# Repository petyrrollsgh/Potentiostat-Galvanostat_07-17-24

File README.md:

# Potentiostat-Galvanostat_07-17-24
KiCad files for the initial Potentiostat-Glavanostat build

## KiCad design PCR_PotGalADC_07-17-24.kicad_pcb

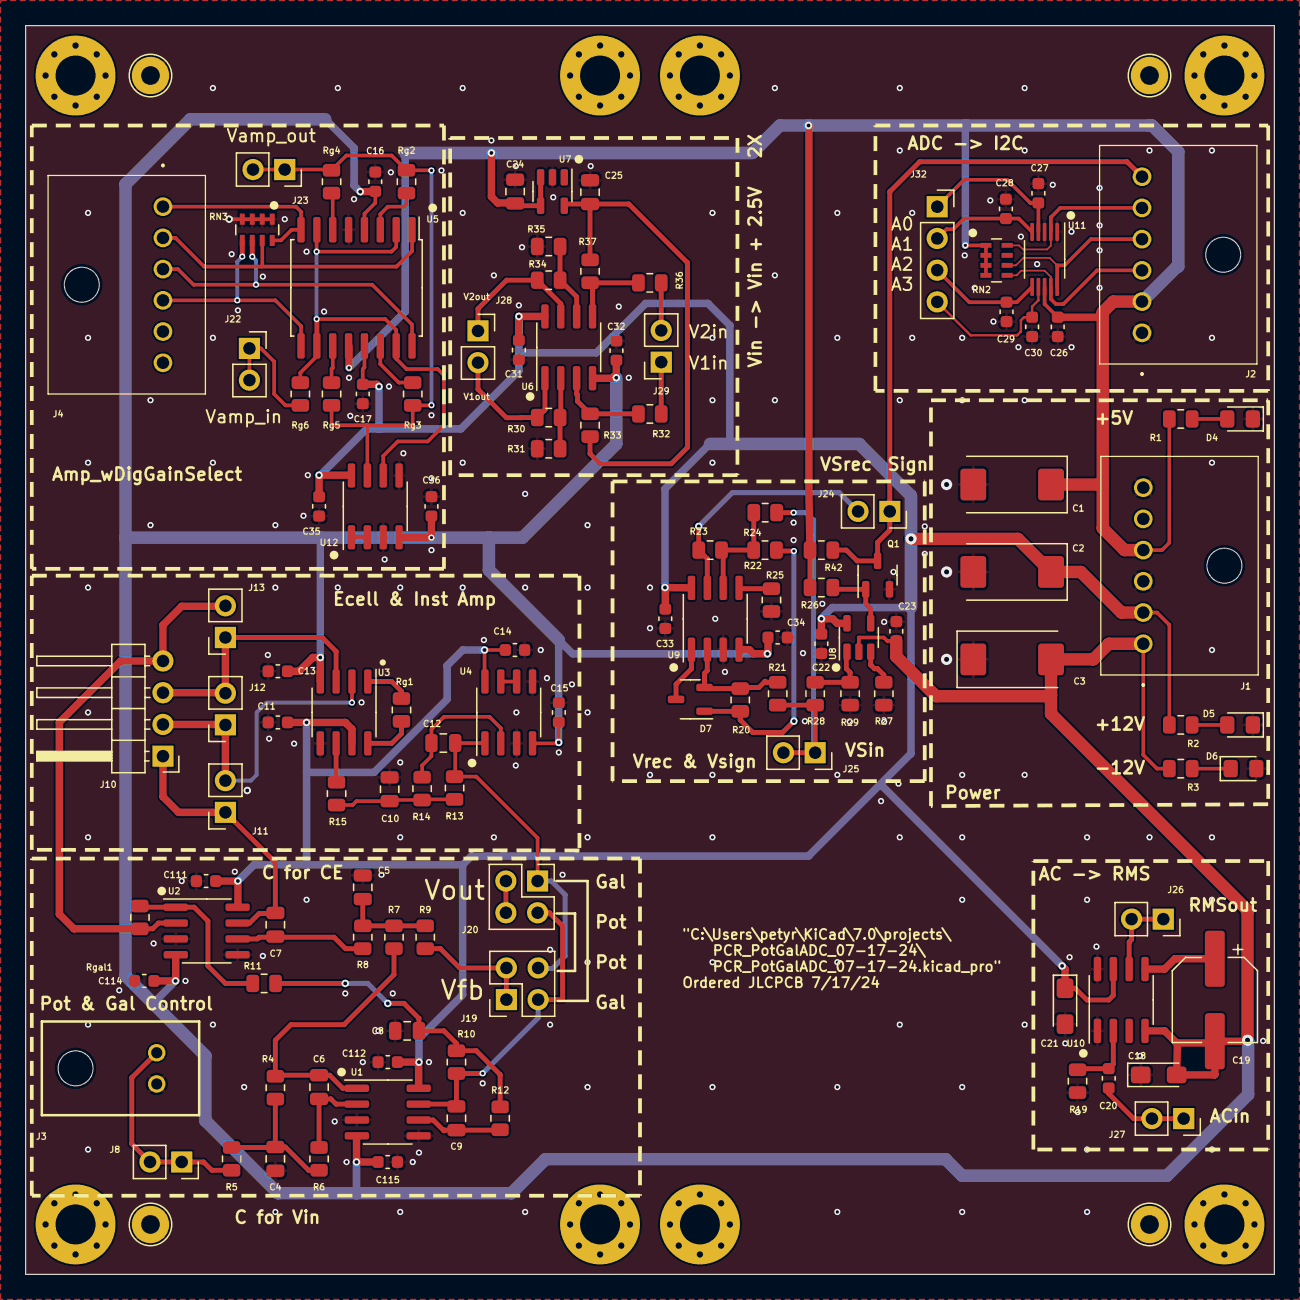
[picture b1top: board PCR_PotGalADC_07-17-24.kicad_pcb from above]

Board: 4 copper layers, 100.0 x 100.0 mm, 133 parts (0 on the bottom side), 73 nets.

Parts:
C1, C2, C3: 47uf; CP_EIA-7343-43_Kemet-X
C4, C5, C8, C10: 390pf; C_0805_2012Metric
C6, C7, C9, C12: 100pf; C_0805_2012Metric
C11, C13, C14, C15, C16, C17, C20, C22, C23, C26, C27, C28, C29, C30, C31, C32, C33, C34, C35, C36, C111, C112, C114, C115: 100nf; C_0603_1608Metric
C18, C21: 1uf; CP_EIA-3216-18_Kemet-A_Pad1.58x1.35mm_HandSolder
C19: 33uf; CP_Elec_6.3x9.9_HandSolder
C24: 1uf; C_0805_2012Metric
C25: 100nf; C_0805_2012Metric
D4: LED-yel; LED_0805_2012Metric_Pad1.15x1.40mm_HandSolder
D5: LED-red; LED_0805_2012Metric_Pad1.15x1.40mm_HandSolder
D6: LED-grn; LED_0805_2012Metric_Pad1.15x1.40mm_HandSolder
D7: BAV99LT1G; SOT-23-3
H1, H2, H3, H4, H5, H6, H7, H8: MountingHole; MountingHole_3.2mm_M3_Pad_Via
J1, J2, J4: TE_EP25-6; Conn_EP25_1744426-6
J3: TE_EP25_2; Conn_EP25_1744426-2
J8, J11, J12, J13, J22, J23, J24, J25, J26, J27, J28, J29: Conn_01x02_Soc; PinSocket_1x02_P2.54mm_Vertical
J10: Conn_01x04_Pin; PinHeader_1x04_P2.54mm_Horizontal
J19, J20: Conn_02x02_Pin; PinHeader_2x02_P2.54mm_Vertical
J32: Conn_01x04; PinSocket_1x04_P2.54mm_Vertical
Q1: BSS138 123-GSD; SOT-23-3
R1, R2, R3, R28: 1k; R_0805_2012Metric
R4, R5, R7, R9, R10, R11, R13, R15, R26, R29, R30, R31, R32, R33, R34, R35, R36, R37, R42: 15k; R_0805_2012Metric
R6, R8, R12, R14: 49R9; R_0805_2012Metric
R19: 1M; R_0805_2012Metric
R20: 4k02; R_0805_2012Metric
R21, R22, R23, R24, R25, R27: 2k05; R_0805_2012Metric
RN2, RN3: R_Pack04_10k; R_Array_Concave_4x0603
Rg1: 0R; R_0805_2012Metric
Rg2: 4k02; R_0805_2012Metric
Rg3: 10k; R_0805_2012Metric
Rg4: 40k2; R_0805_2012Metric
Rg5: 20k; R_0805_2012Metric
Rg6: 2k05; R_0805_2012Metric
Rgal1: 1k; R_0805_2012Metric
TPG1, TPG2, TPG3, TPG4: 5006; TestPoint_Loop_D2.54mm_Drill1.5mm_Beaded
U1, U4, U6, U9, U12: OPA1656; SOIC-8_3.9x4.9mm_P1.27mm
U2: THS4012; SOIC-8_3.9x4.9mm_P1.27mm
U3: INA129; SOIC-8_3.9x4.9mm_P1.27mm
U5: MAX4662; SOIC-16W_7.5x10.3mm_P1.27mm
U7: LM4132xMF-2.5; SOT-23-5
U8: TL331; SOT-23-5
U10: AD736JNZ; SOIC-8_3.9x4.9mm_P1.27mm
U11: ADS1015IDGS; VSSOP-10_3x3mm_P0.5mm

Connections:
+5V: C1.1, C24.2, C26.1, J1.4, J2.2, R1.1, R26.2, R42.2, RN2.1 (R1.1), RN2.2 (R2.1), RN2.3 (R3.1), RN2.4 (R4.1), U5.12 (VL), U7.3 (EN), U7.4 (VIN), U11.8 (VDD)
+12V: C2.1, C11.2, C14.2, C17.2, C21.1, C22.2, C31.2, C33.2, C35.2, C111.2, C112.2, J1.2, R2.1, U1.8 (V+), U2.8 (V+), U3.7 (V+), U4.8 (V+), U5.13 (V+), U6.8 (V+), U8.5 (V+), U9.8 (V+), U10.7 (+VS), U12.8 (V+)
-12V: C3.2, C13.2, C15.2, C16.2, C18.2, C19.2, C23.2, C32.2, C34.2, C36.2, C114.2, C115.2, J1.1, R3.1, U1.4 (V-), U2.4 (V-), U3.4 (V-), U4.4 (V-), U5.4 (V-), U6.4 (V-), U8.2 (V-), U9.4 (V-), U10.4 (-VS), U12.4 (V-)
/2.5V_Offset_X2/V1in: J29.1, R32.2
/2.5V_Offset_X2/V1out: J28.2, R30.2, U6.1
/2.5V_Offset_X2/V2in: J29.2, R36.2
/2.5V_Offset_X2/V2out: J28.1, R34.2, U6.7
/2.5V_Offset_X2/m1: R30.1, R31.2, U6.2 (-)
/2.5V_Offset_X2/m2: R32.1, R33.2, U6.3 (+)
/2.5V_Offset_X2/m3: R34.1, R35.2, U6.6 (-)
/2.5V_Offset_X2/m4: R36.1, R37.2, U6.5 (+)
/2V5: C25.2, R33.1, R37.1, U7.5 (VREF)
/A0: C27.1, J32.1, U11.4 (AIN0)
/A1: C28.1, J32.2, U11.5 (AIN1)
/A2: C29.1, J32.3, U11.6 (AIN2)
/A3: C30.1, J32.4, U11.7 (AIN3)
/AC2RMS/i: C20.2, R19.2, U10.2 (VIN)
/AC2RMS/j: C19.1, U10.5 (CAV)
/AmpLogicArray/com: Rg6.1, U5.2 (COM1), U5.7 (COM4), U5.10 (COM3), U5.15 (COM2), U12.6 (-)
/RMSin: C20.1, J27.1, J27.2
/RMSout: J26.1, J26.2, U10.6 (OUT)
/SigRect/ac: R28.1, R29.2, U8.1 (-)
/SigRect/t0: D7.3 (common), U9.1
/SigRect/t1: D7.2 (K), R20.1, R21.2, U9.2 (-)
/SigRect/t2: D7.1 (A), R20.2, R22.2
/SigRect/t3: R22.1, R23.1, R24.2, U9.6 (-)
/SigRect/t4: R25.2, U9.5 (+)
/SigRect/t5: R27.1, U8.3 (+)
/SigRect/t9: Q1.1 (G), R26.1, U8.4
/VSin: J25.1, J25.2, R21.1, R24.1, R28.2
/VSout: J24.2, R23.2, U9.7
/Vamp_in: J22.1, J22.2, Rg6.2
/Vamp_out: J23.1, J23.2, Rg2.1, Rg3.2, Rg4.1, Rg5.2, U12.7
/Vgal: C9.2, J19.3, J20.2, R10.1, U1.7
/Vpot: C12.2, J19.4, J20.1, R13.1, U4.1
/c1: C5.2, R7.1, R8.2, R9.1
/c2: C7.1, R8.1, U2.6 (-)
/g1: Rg1.2, U3.8 (Rg)
/g2: Rg1.1, U3.1 (Rg)
/k1: C10.2, R13.2, R14.2, R15.1
/k2: C12.1, R14.1, U4.2 (-)
/v1: C4.2, R4.1, R5.2, R6.2
/v2: C6.1, R6.1, U1.2 (-)
/w1: R11.2, Rgal1.2, U2.1
/w2: C8.2, R10.2, R11.1, R12.2
/w3: C9.1, R12.1, U1.6 (-)
ALERT: J2.5, RN2.8 (R1.2), U11.2 (ALERT/RDY)
CE: C7.2, J10.1, J11.1, U2.7
GNDA: C1.2, C2.2, C3.1, C4.1, C5.1, C8.1, C10.1, C11.1, C13.1, C14.1, C15.1, C16.1, C17.1, C18.1, C21.2, C22.1, C23.1, C24.1, C25.1, C26.2, C27.2, C28.2, C29.2, C30.2, C31.1, C32.1, C33.1, C34.1, C35.1, C36.1, C111.1, C112.1, C114.1, C115.1, D4.1 (K), D5.1 (K), D6.2 (A), J1.3, J1.6, J2.1, J3.1, Q1.2 (S), R19.1, R25.1, R27.2, R29.1, R31.1, R35.1, RN3.5 (R4.2), RN3.6 (R3.2), RN3.7 (R2.2), RN3.8 (R1.2), TPG1.1, TPG2.1, TPG3.1, TPG4.1, U1.3 (+), U1.5 (+), U2.3 (+), U2.5 (+), U3.5 (Ref), U4.3 (+), U4.5 (+), U5.5 (GND), U7.2 (GND), U9.3 (+), U10.1 (CC), U10.8 (COM), U11.1 (ADDR), U11.3 (GND), U12.3 (+), U12.5 (+)
unnamed: C6.2, R4.2, R7.2, U1.1
unnamed: D4.2 (A), R1.2
unnamed: D5.2 (A), R2.2
unnamed: D6.1 (K), R3.2
unnamed: R15.2, U3.6
unnamed: U4.6 (-), U4.7
unnamed: Rg2.2, U5.3 (NO1)
unnamed: Rg3.1, U5.14 (NO2)
unnamed: Rg5.1, U5.11 (NO3)
unnamed: Rg4.2, U5.6 (NO4)
unnamed: U12.1, U12.2 (-)
RE: J10.2, J11.2, J12.1, U3.2 (-)
SCL: J2.4, RN2.6 (R3.2), U11.10 (SCL)
SDA: J2.3, RN2.5 (R4.2), U11.9 (SDA)
SE: J10.3, J12.2, J13.1, U3.3 (+)
SelR0: J4.4, RN3.1 (R1.1), U5.9 (IN3)
SelR1: J4.3, RN3.2 (R2.1), U5.16 (IN2)
SelR2: J4.2, RN3.3 (R3.1), U5.1 (IN1)
SelR3: J4.1, RN3.4 (R4.1), U5.8 (IN4)
Sign: J2.6, J24.1, Q1.3 (D), R42.1
Vfb: J19.1, J19.2, R9.2
Vin1: J3.2, J8.1, J8.2, R5.1
Vout: J20.3, J20.4
WE: J10.4, J13.2, Rgal1.1, U2.2 (-)
